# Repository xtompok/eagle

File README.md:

eagle
=====

Eagle files for various projects

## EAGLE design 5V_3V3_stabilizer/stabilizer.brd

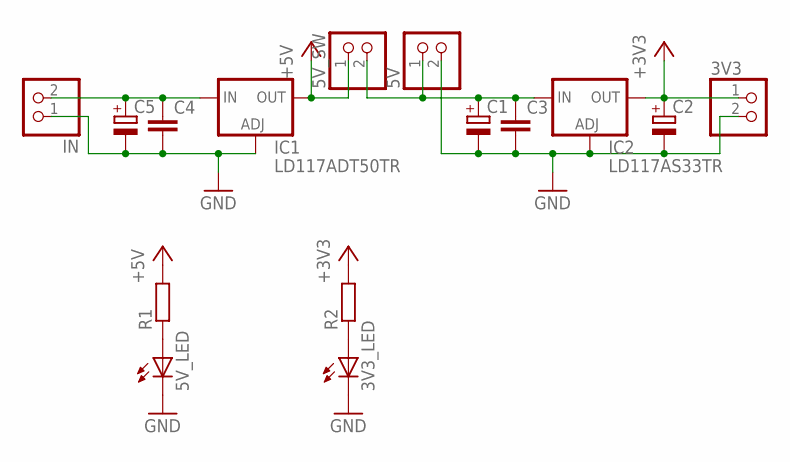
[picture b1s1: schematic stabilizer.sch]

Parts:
3V3, 5V, 5V_SW: PINHD-1X2; 1X02
3V3_LED, 5V_LED: LEDSML0805; SML0805
C1, C2, C5: CPOL-EUD; PANASONIC_D
C3, C4: C-EUC0805; C0805
IC1: LD117ADT50TR; DPACK
IC2: LD117AS33TR; SOT223
IN: PINHD-1X2; 1X02
R1, R2: R-EU_R0805; R0805

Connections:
+3V3: 3V3.1, C2.+, IC2.4 (OUT), R2.2
+5V: 5V_SW.1, IC1.4 (OUT), R1.2
GND: 3V3.2, 3V3_LED.C, 5V.2, 5V_LED.C, C1.-, C2.-, C3.2, C4.2, C5.-, IC1.1 (ADJ), IC2.1 (ADJ), IN.1
unnamed: 5V_LED.A, R1.1
unnamed: 3V3_LED.A, R2.1
unnamed: C4.1, C5.+, IC1.3 (IN), IN.2
unnamed: 5V.1, 5V_SW.2, C1.+, C3.1, IC2.3 (IN)

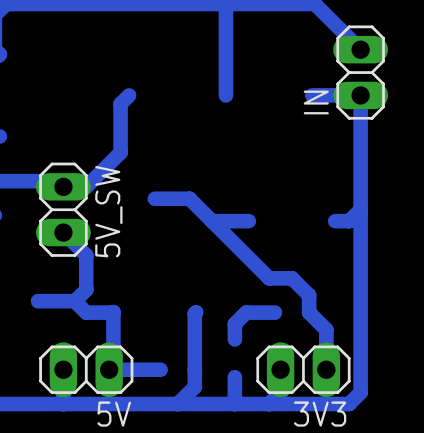
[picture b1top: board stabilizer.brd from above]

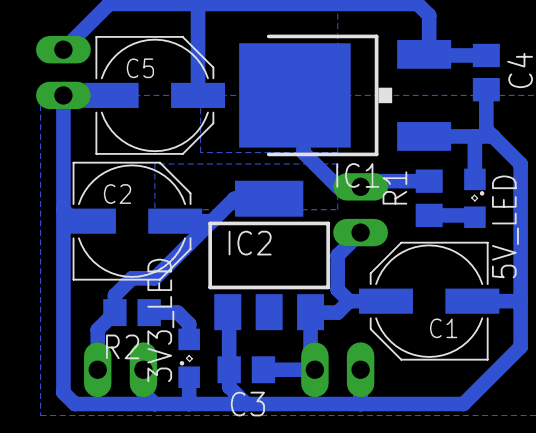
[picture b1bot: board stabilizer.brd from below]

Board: 2 copper layers, 15 parts (11 on the bottom side), 7 nets.

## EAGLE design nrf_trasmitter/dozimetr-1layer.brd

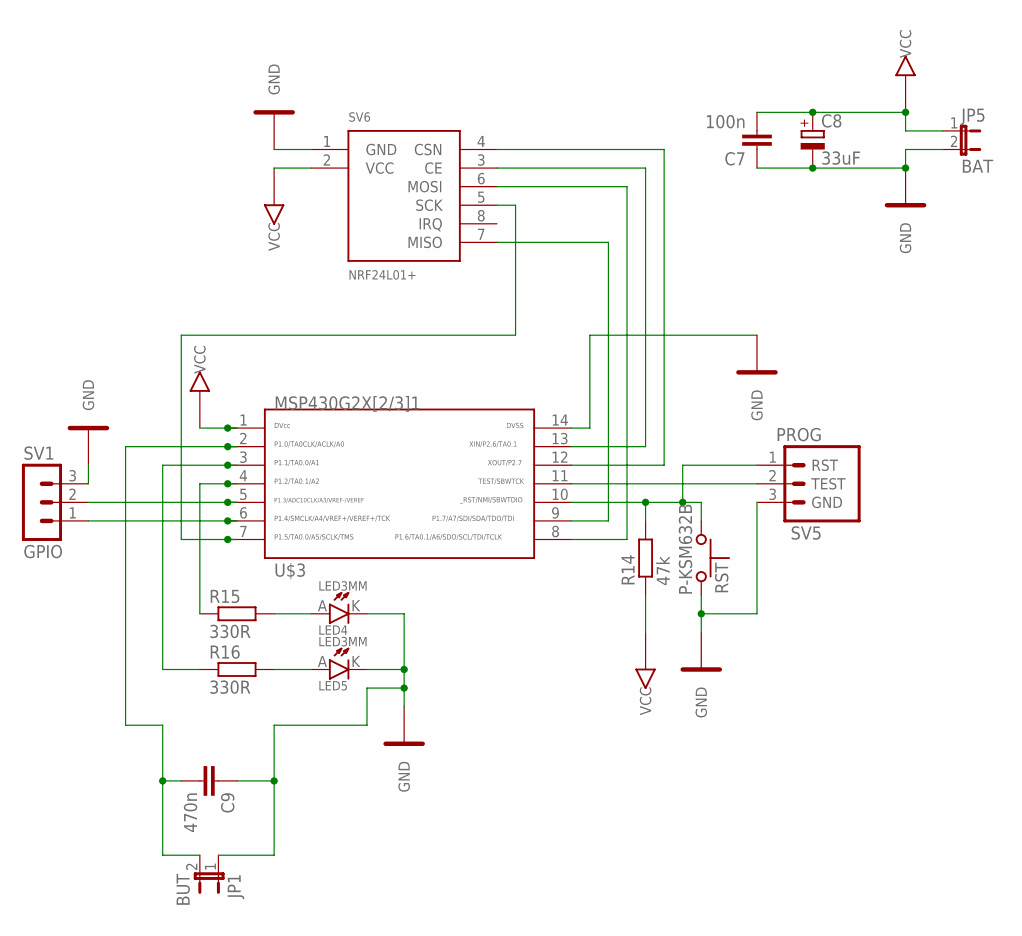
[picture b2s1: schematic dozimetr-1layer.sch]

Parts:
C7: 100n; C0805
C8: 33uF; E2,5-6E
C9: 470n; C0805K
JP1: BUT; JP1
JP5: BAT; JP1
LED4, LED5: LED3MM
R14: 47k; R0805
R15, R16: 330R; R0805
RST: P-KSM632B
SV1: GPIO; MA03-1
SV5: PROG; MA03-1
SV6: NRF24L01+; NRF24L01_MOD
U$3: G2X[2/3]1---PW14; PW14

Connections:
GND: C7.1, C8.-, C9.1, JP1.1, JP5.2, LED4.K (C), LED5.K (C), RST.2, SV1.3, SV5.3 (GND), SV6.1 (GND), U$3.14
unnamed: C9.2, JP1.2, U$3.2
unnamed: SV1.2, U$3.5
unnamed: SV1.1, U$3.6
unnamed: SV5.2 (TEST), U$3.11
unnamed: R14.2, RST.1, SV5.1 (RST), U$3.10
unnamed: SV6.7 (MISO), U$3.9
unnamed: SV6.6 (MOSI), U$3.8
unnamed: SV6.5 (SCK), U$3.7
unnamed: R15.1, U$3.4
unnamed: LED4.A, R15.2
unnamed: SV6.3 (CE), U$3.13
unnamed: SV6.4 (CSN), U$3.12
unnamed: R16.1, U$3.3
unnamed: LED5.A, R16.2
VCC: C7.2, C8.+, JP5.1, R14.1, SV6.2 (VCC), U$3.1

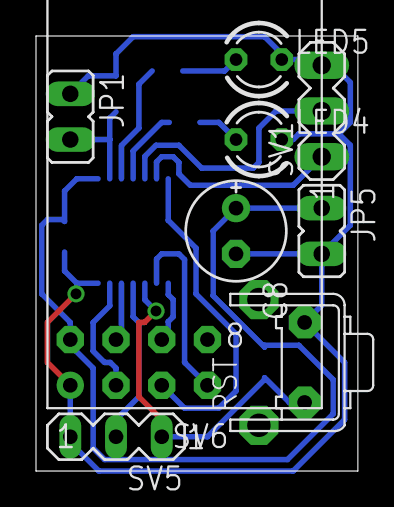
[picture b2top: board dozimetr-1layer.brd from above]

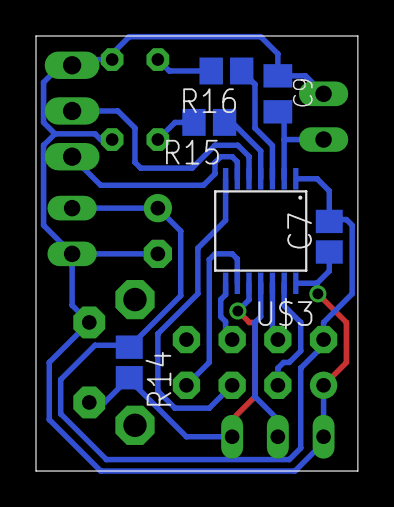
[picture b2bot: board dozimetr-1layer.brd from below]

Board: 2 copper layers, 17.9 x 24.2 mm, 15 parts (6 on the bottom side), 16 nets.

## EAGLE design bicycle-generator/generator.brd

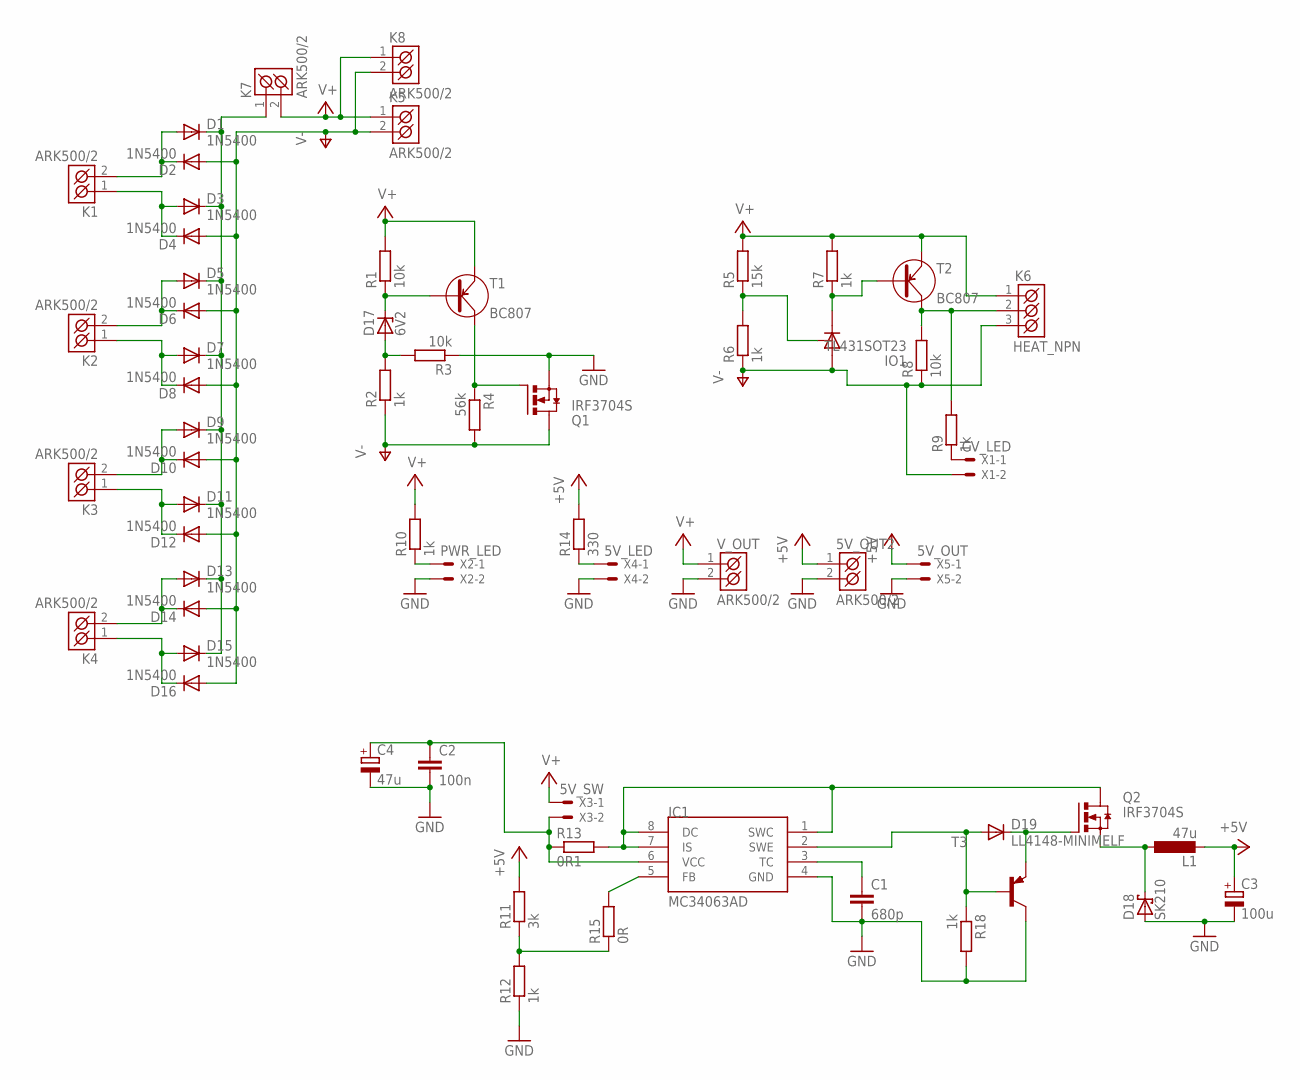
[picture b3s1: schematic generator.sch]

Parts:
5V_OUT2: ARK500/2
C1: 680p; C0805
C2: 100n; C0805
C3: 100u; PANASONIC_D
C4: 47u; PANASONIC_D
D1, D2, D3, D4, D5, D6, D7, D8, D9, D10, D11, D12, D13, D14, D15, D16: 1N5400; DO201-15
D17: 6V2; SOD80C
D18: SK210; SMB
D19: LL4148-MINIMELF; SOD80C
IC1: MC34063AD; SOIC8
IO1: TL431SOT23; SOT23
K1, K2, K3, K4, K5, K7, K8: ARK500/2
K6: HEAT_NPN; ARK500/3
L1: 47u; TJ3-U1
Q1, Q2: IRF3704S; D2PACK
R1, R3, R8: 10k; R0805
R2, R6, R7, R9, R10, R12, R18: 1k; R0805
R4: 56k; R0805
R5: 15k; R0805
R11: 3k; R0805
R13: 0R1; R0805
R14: 330; R0805
R15: 0R; R1206
T1, T2: BC807; SOT-23
T3: BC807-16-PNP-SOT23-BEC; SOT23-BEC
V_OUT: ARK500/2
X1: CV_LED; 22-23-2021
X2: PWR_LED; 22-23-2021
X3: 5V_SW; 22-23-2021
X4: 5V_LED; 22-23-2021
X5: 5V_OUT; 22-23-2021

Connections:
+5V: 5V_OUT2.1 (K1), C3.+, L1.2, R11.2, R14.2, X5.1
GND: 5V_OUT2.2 (K2), C1.2, C2.2, C3.-, C4.-, D18.A, IC1.4 (GND), Q1.3 (S), R3.1, R12.1, R18.2, T3.C, V_OUT.2 (K2), X2.2, X4.2, X5.2
unnamed: D1.A, D2.C, K1.2 (K2)
unnamed: D3.A, D4.C, K1.1 (K1)
unnamed: IO1.1 (C), R7.1, T2.1 (B)
unnamed: Q1.1 (G), R4.1, T1.3 (C)
unnamed: D5.A, D6.C, K2.2 (K2)
unnamed: D7.A, D8.C, K2.1 (K1)
unnamed: K6.2 (K2), R8.2, R9.2, T2.3 (C)
unnamed: R9.1, X1.1
unnamed: D9.A, D10.C, K3.2 (K2)
unnamed: D11.A, D12.C, K3.1 (K1)
unnamed: R11.1, R12.2, R15.1
unnamed: IO1.2 (R), R5.1, R6.2
unnamed: D13.A, D14.C, K4.2 (K2)
unnamed: D15.A, D16.C, K4.1 (K1)
unnamed: D19.C, Q2.1 (G), T3.E
unnamed: C1.1, IC1.3 (TC)
unnamed: D17.C, R1.1, T1.1 (B)
unnamed: D17.A, R2.2, R3.2
unnamed: D18.C, L1.1, Q2.3 (S)
unnamed: D1.C, D3.C, D5.C, D7.C, D9.C, D11.C, D13.C, D15.C, K7.1 (K1)
unnamed: IC1.5 (FB), R15.2
unnamed: R14.1, X4.1
unnamed: R10.1, X2.1
unnamed: C2.1, C4.+, IC1.6 (VCC), R13.1, X3.2
unnamed: IC1.1 (SWC), IC1.7 (IS), IC1.8 (DC), Q2.2 (D), R13.2
unnamed: D19.A, IC1.2 (SWE), R18.1, T3.B
V+: K5.1 (K1), K6.1 (K1), K7.2 (K2), K8.1 (K1), R1.2, R5.2, R7.2, R10.2, T1.2 (E), T2.2 (E), V_OUT.1 (K1), X3.1
V-: D2.A, D4.A, D6.A, D8.A, D10.A, D12.A, D14.A, D16.A, IO1.3 (A), K5.2 (K2), K6.3 (K3), K8.2 (K2), Q1.2 (D), R2.1, R4.2, R6.1, R8.1, X1.2

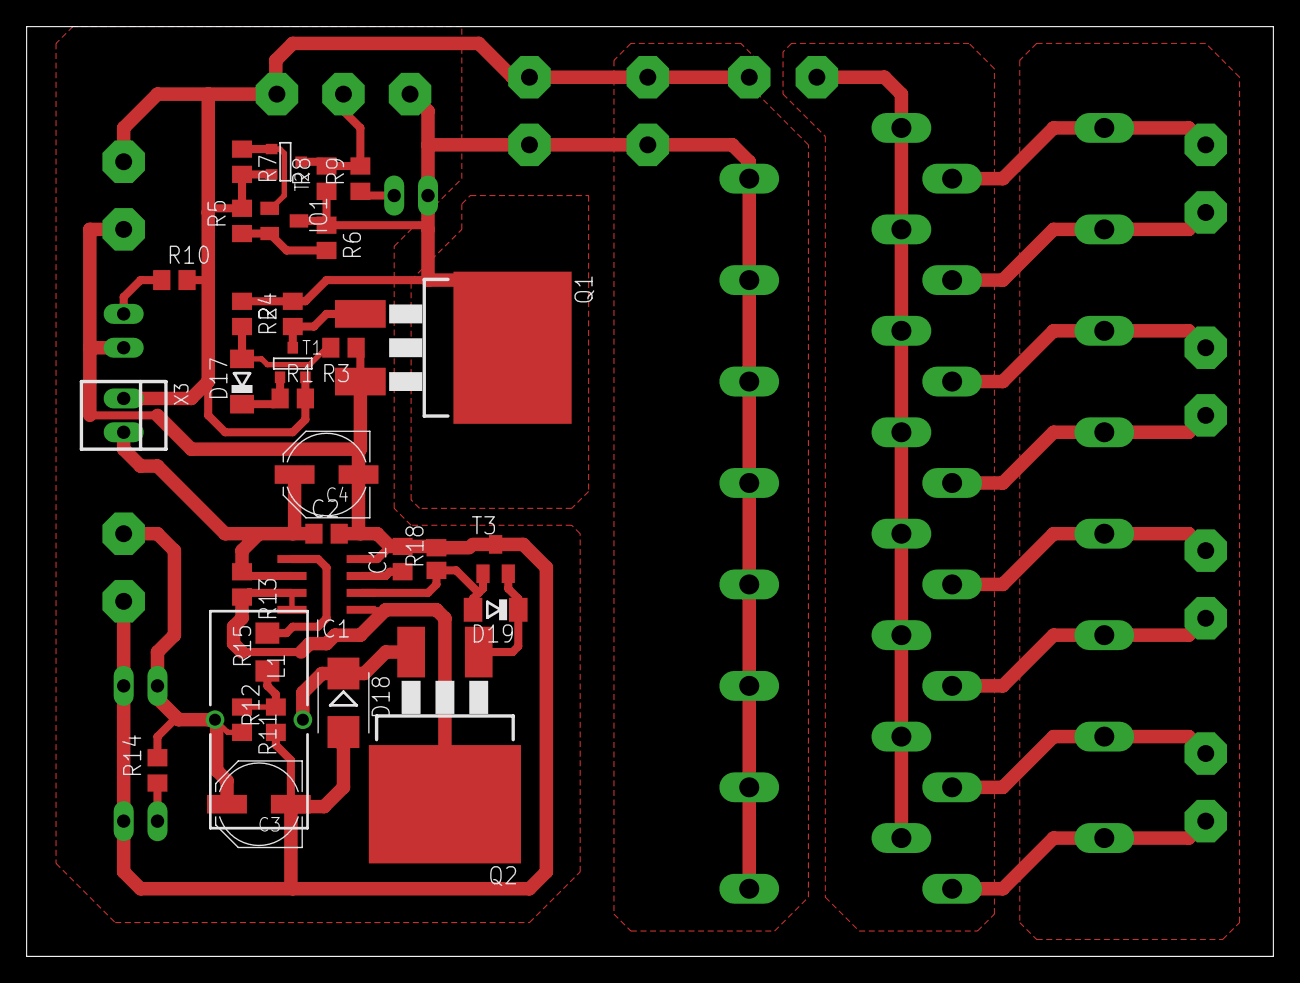
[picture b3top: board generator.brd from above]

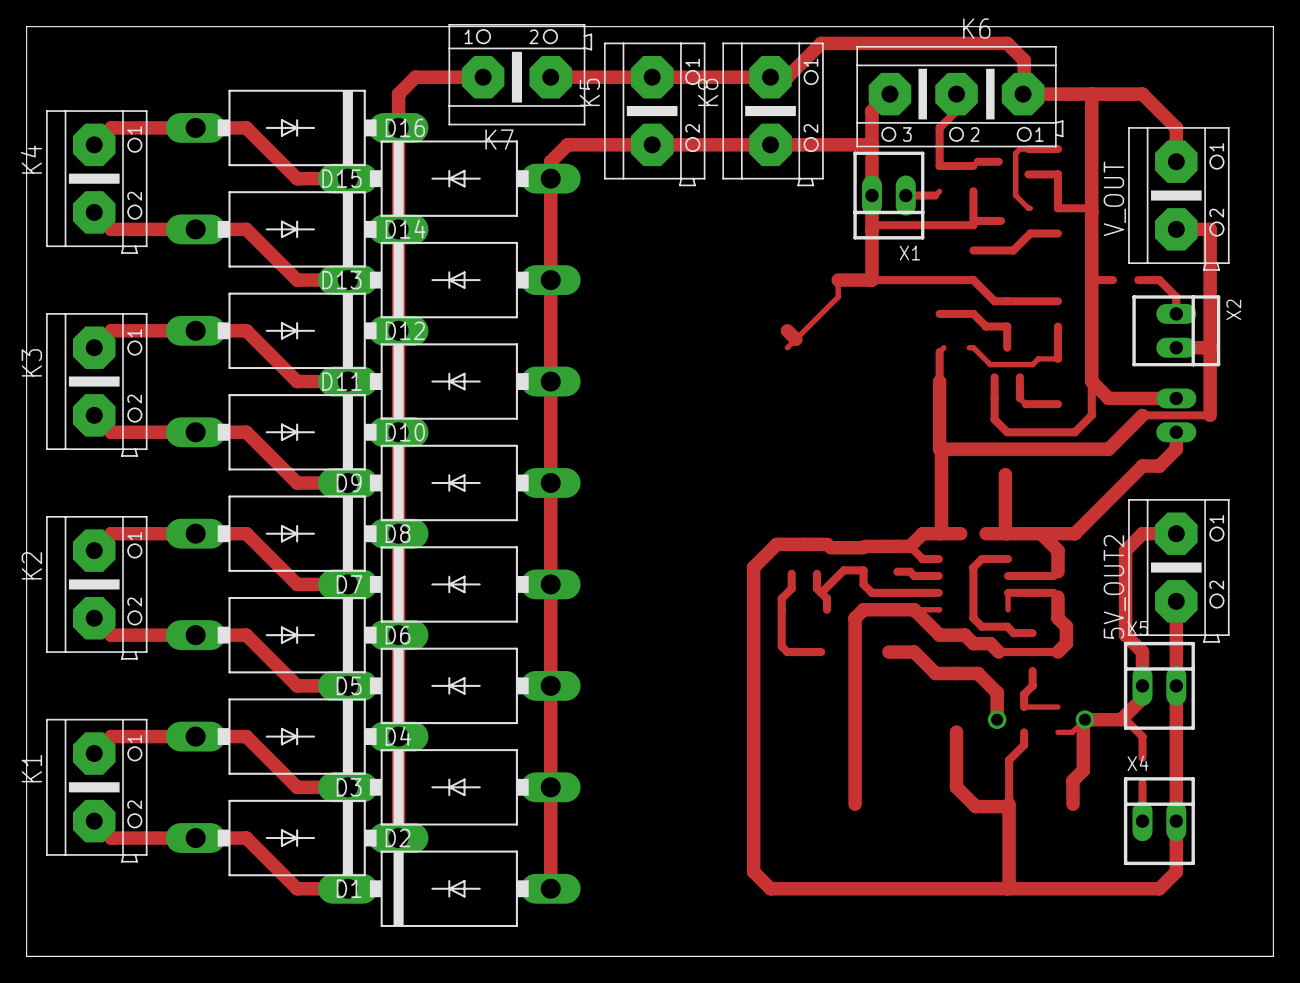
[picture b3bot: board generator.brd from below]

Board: 2 copper layers, 93.7 x 69.8 mm, 62 parts (30 on the bottom side), 30 nets.

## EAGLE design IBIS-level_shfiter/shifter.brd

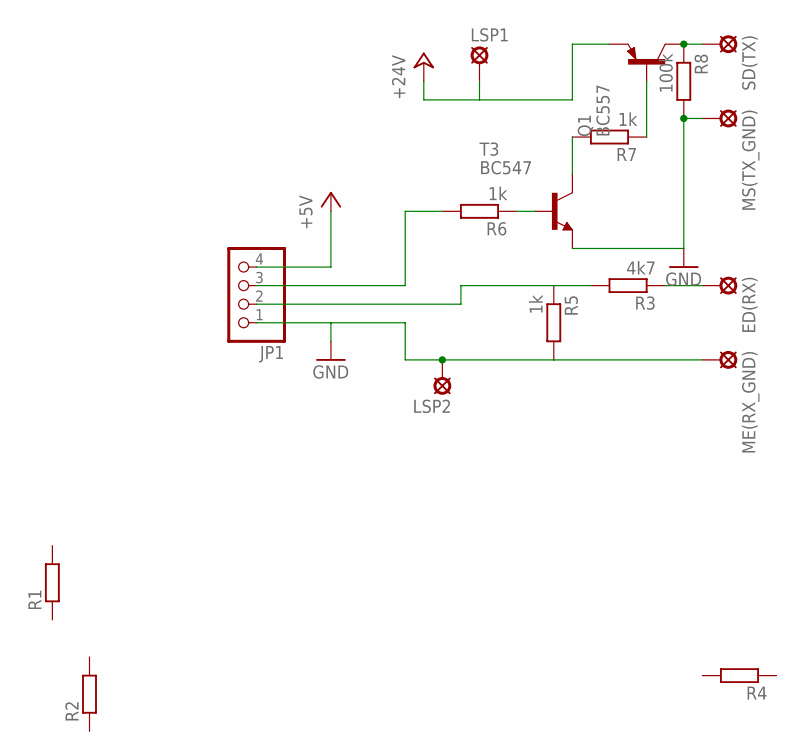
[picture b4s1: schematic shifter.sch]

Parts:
ED(RX): LSP10
JP1: PINHD-1X4; 1X04
LSP1, LSP2: LSP10
ME(RX_GND): LSP10
MS(TX_GND): LSP10
Q1: BC557; TO92
R1, R2, R4: R-EU_M0805; M0805
R3: 4k7; M0805
R5, R6, R7: 1k; M0805
R8: 100k; M0805
SD(TX): LSP10
T3: BC547; TO92

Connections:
+5V: JP1.4
+24V: LSP1.MP, Q1.1 (E)
GND: JP1.1, LSP2.MP, ME(RX_GND).MP, MS(TX_GND).MP, R5.2, R8.2, T3.1 (E)
unnamed: ED(RX).MP, R3.1
unnamed: JP1.2, R3.2, R5.1
unnamed: JP1.3, R6.2
unnamed: R6.1, T3.2 (B)
unnamed: R7.2, T3.3 (C)
unnamed: Q1.2 (B), R7.1
unnamed: Q1.3 (C), R8.1, SD(TX).MP

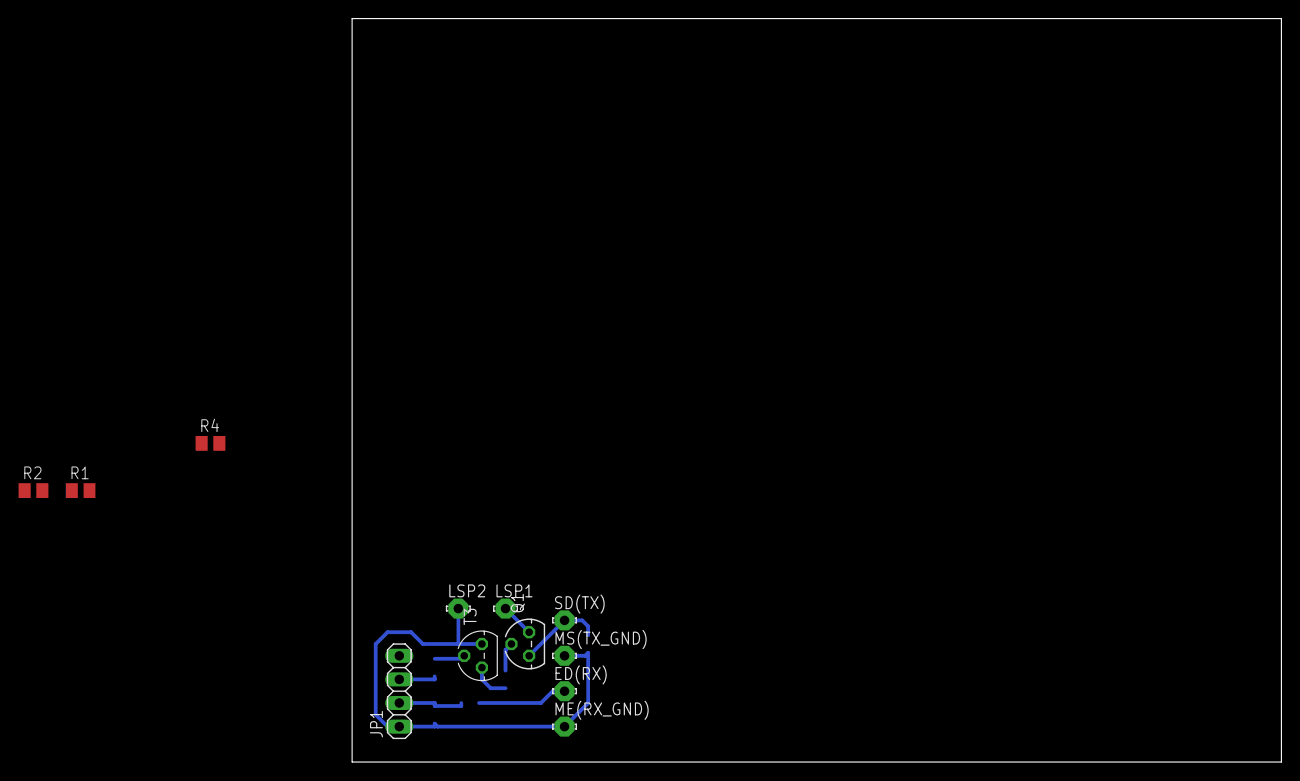
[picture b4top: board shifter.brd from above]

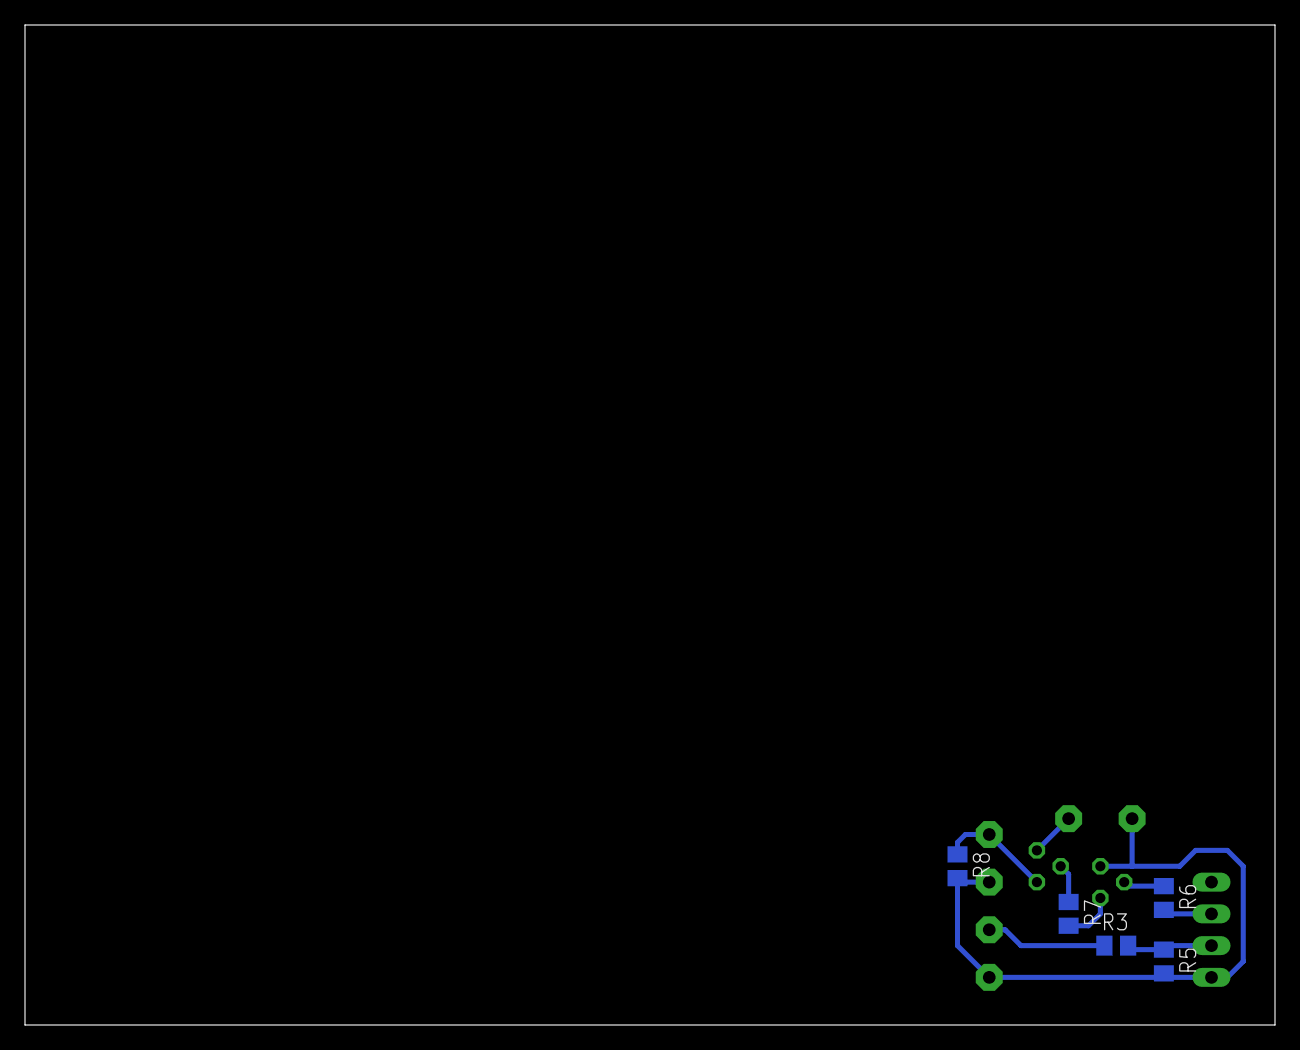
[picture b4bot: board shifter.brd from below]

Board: 2 copper layers, 100.0 x 80.0 mm, 17 parts (5 on the bottom side), 9 nets.

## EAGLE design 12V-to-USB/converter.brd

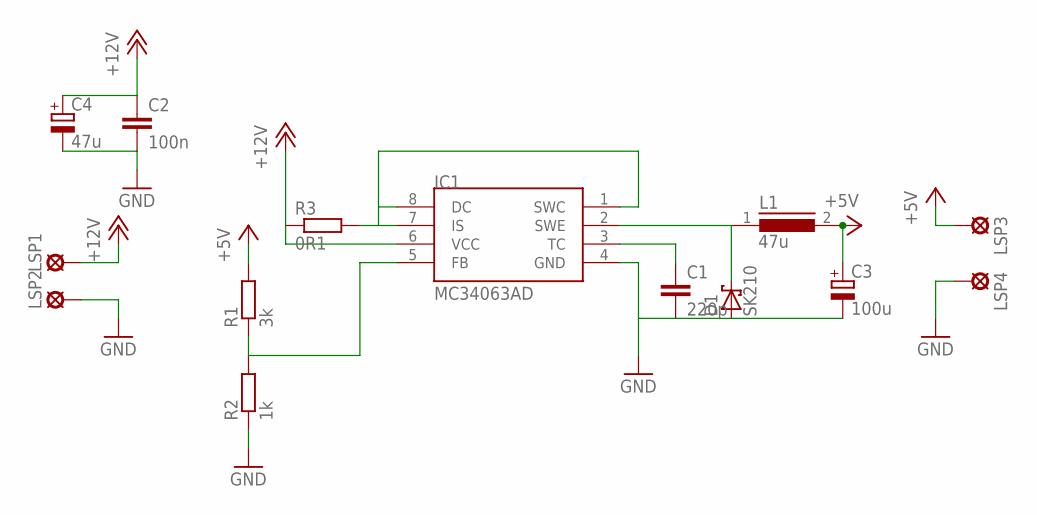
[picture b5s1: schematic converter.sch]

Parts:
C1: 220p; C0805
C2: 100n; C0805
C3: 100u; PANASONIC_D
C4: 47u; PANASONIC_D
D1: SK210; SMB
IC1: MC34063AD; SOIC8
L1: 47u; DR127
LSP1: +12V; LSP11
LSP2: GND; LSP11
LSP3, LSP4: LSP11
R1: 3k; R0805
R2: 1k; R0805
R3: 0R1; R0805

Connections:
+5V: C3.+, L1.2, LSP3.MP, R1.2
+12V: C2.1, C4.+, IC1.6 (VCC), LSP1.MP, R3.1
GND: C1.2, C2.2, C3.-, C4.-, D1.A, IC1.4 (GND), LSP2.MP, LSP4.MP, R2.1
unnamed: IC1.5 (FB), R1.1, R2.2
unnamed: IC1.1 (SWC), IC1.7 (IS), IC1.8 (DC), R3.2
unnamed: C1.1, IC1.3 (TC)
unnamed: D1.C, IC1.2 (SWE), L1.1

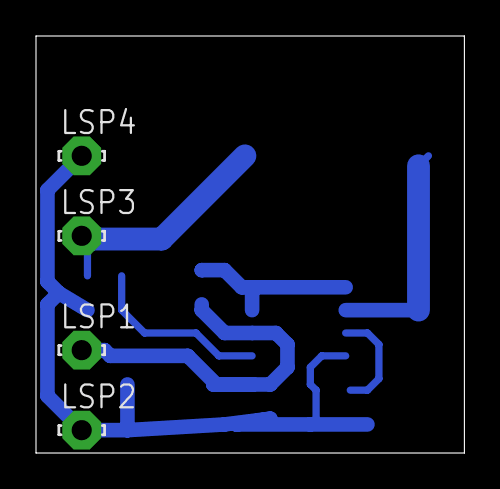
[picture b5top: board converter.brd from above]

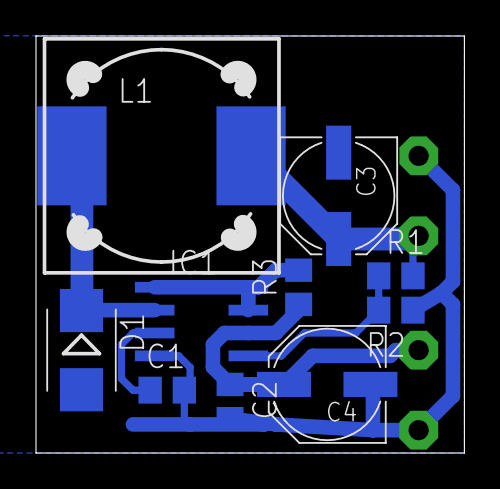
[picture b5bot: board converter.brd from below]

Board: 2 copper layers, 23.8 x 23.2 mm, 14 parts (10 on the bottom side), 7 nets.

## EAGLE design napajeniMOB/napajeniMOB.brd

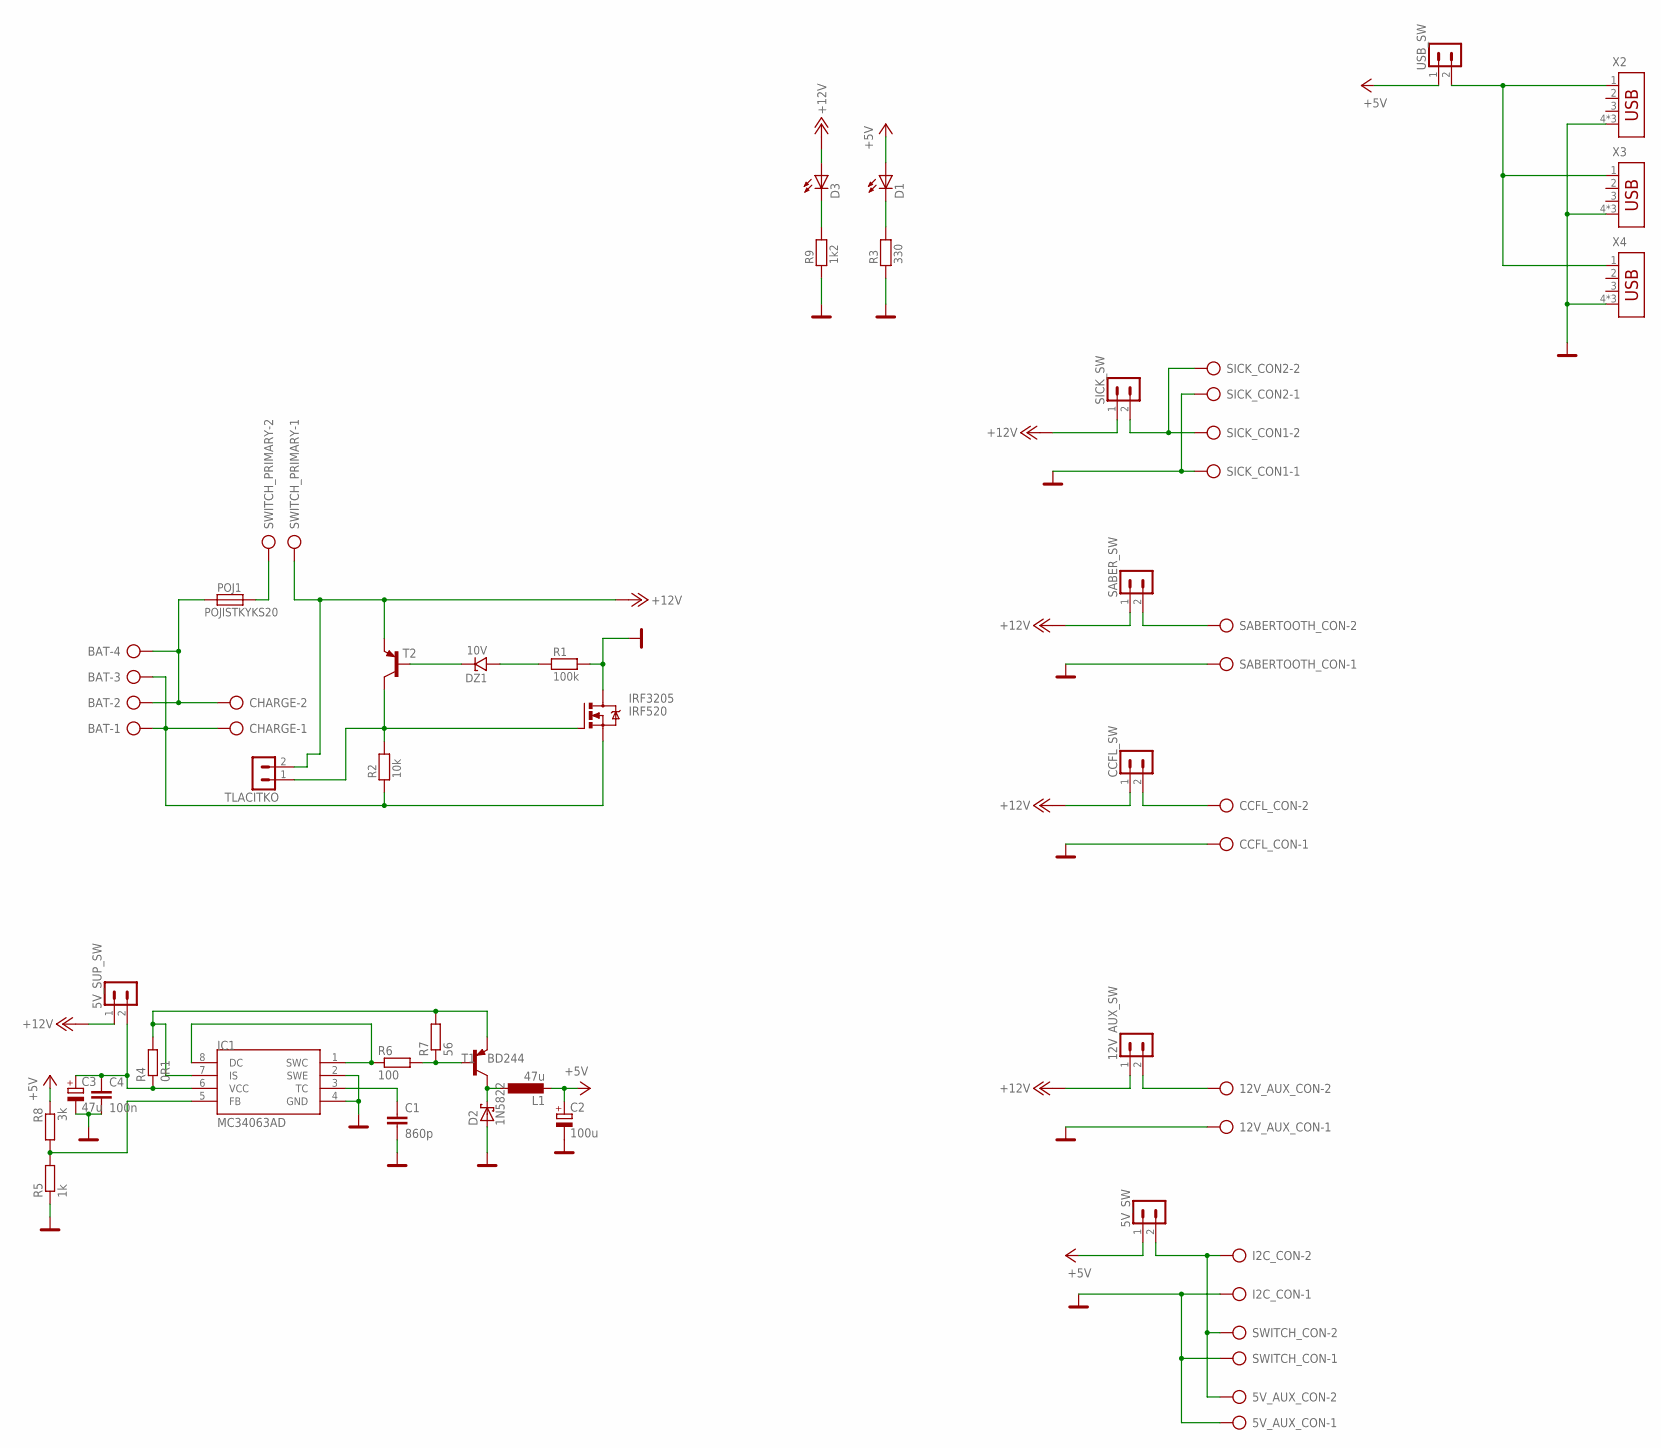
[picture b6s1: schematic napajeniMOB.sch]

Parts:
5V_AUX_CON, 12V_AUX_CON: AK500/2
5V_SUP_SW, 5V_SW, 12V_AUX_SW: PSH02-02P
BAT: AK500/4
C1: 860p; C0805
C2: 100u; E5-8,5
C3: 47u; E5-8,5
C4: 100n; C0805
CCFL_CON: AK500/2
CCFL_SW: PSH02-02P
CHARGE: AK500/2
D1, D3: LED3MM
D2: 1N5822; DO41-7.6
DZ1: 10V; SOD-80
I2C_CON: AK500/2
IC1: MC34063AD; SOIC8
IRF3205: IRF520; TO220BV
L1: 47u; TJ3-U1
POJ1: POJISTKYKS20; POJ_KS20
R1: 100k; 0805
R2: 10k; 0805
R3: 330; 0805
R4: 0R1; M0805
R5: 1k; M0805
R6: 100; M0805
R7: 56; M0805
R8: 3k; M0805
R9: 1k2; 0805
SABERTOOTH_CON: AK500/2
SABER_SW: PSH02-02P
SICK_CON1, SICK_CON2: AK500/2
SICK_SW: PSH02-02P
SWITCH_CON: AK500/2
SWITCH_PRIMARY: AK500/2
T1: BD244; TO220
T2: BC807-16-PNP-SOT23-BEC; SOT23-BEC
TLACITKO: PSH02-02P
USB_SW: PSH02-02P
X2, X3, X4: USB-787616GROUNDED; USBGROUNDED

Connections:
+5V: 5V_SW.1, C2.+, D1.A, L1.2, R8.1, USB_SW.1
+12V: 5V_SUP_SW.1, 12V_AUX_SW.1, CCFL_SW.1, D3.A, SABER_SW.1, SICK_SW.1, SWITCH_PRIMARY.1, T2.E, TLACITKO.2
GND: 5V_AUX_CON.1, 12V_AUX_CON.1, C1.2, C2.-, C3.-, C4.2, CCFL_CON.1, D2.A, I2C_CON.1, IC1.2 (SWE), IC1.4 (GND), IRF3205.D, R1.2, R3.1, R5.1, R9.1, SABERTOOTH_CON.1, SICK_CON1.1, SICK_CON2.1, SWITCH_CON.1, X2.4, X2.S1 (4), X2.S2 (4), X3.4, X3.S1 (4), X3.S2 (4), X4.4, X4.S1 (4), X4.S2 (4)
GND_BATERIE: BAT.1, BAT.3, CHARGE.1, IRF3205.S, R2.1
unnamed: DZ1.A, R1.1
unnamed: BAT.2, BAT.4, CHARGE.2, POJ1.1
unnamed: DZ1.K, T2.B
unnamed: POJ1.2, SWITCH_PRIMARY.2
unnamed: IRF3205.G, R2.2, T2.C, TLACITKO.1
unnamed: 5V_SUP_SW.2, C3.+, C4.1, IC1.6 (VCC), R4.1
unnamed: D3.K (C), R9.2
unnamed: D1.K (C), R3.2
unnamed: SICK_CON1.2, SICK_CON2.2, SICK_SW.2
unnamed: USB_SW.2, X2.1, X3.1, X4.1
unnamed: SABERTOOTH_CON.2, SABER_SW.2
unnamed: CCFL_CON.2, CCFL_SW.2
unnamed: D2.C, L1.1, T1.2 (C)
unnamed: 12V_AUX_CON.2, 12V_AUX_SW.2
unnamed: 5V_AUX_CON.2, 5V_SW.2, I2C_CON.2, SWITCH_CON.2
unnamed: IC1.5 (FB), R5.2, R8.2
unnamed: IC1.7 (IS), R4.2, R7.2, T1.3 (E)
unnamed: IC1.1 (SWC), IC1.8 (DC), R6.1
unnamed: R6.2, R7.1, T1.1 (B)
unnamed: C1.1, IC1.3 (TC)

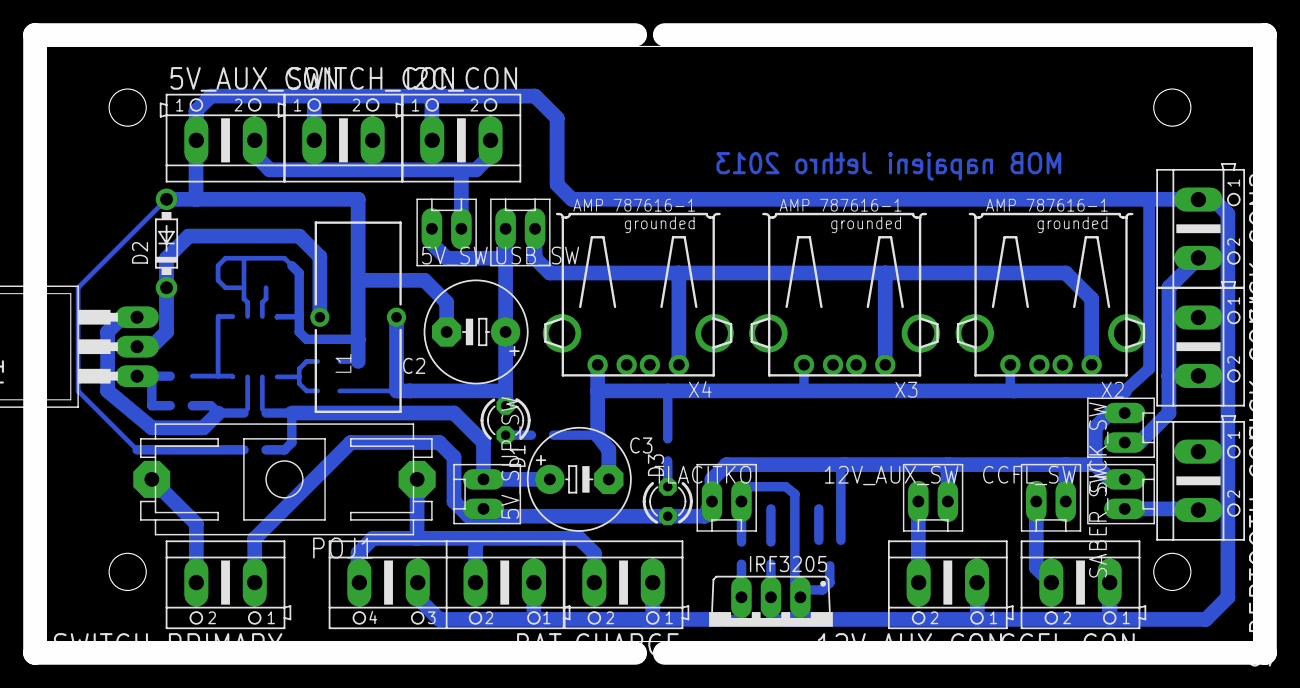
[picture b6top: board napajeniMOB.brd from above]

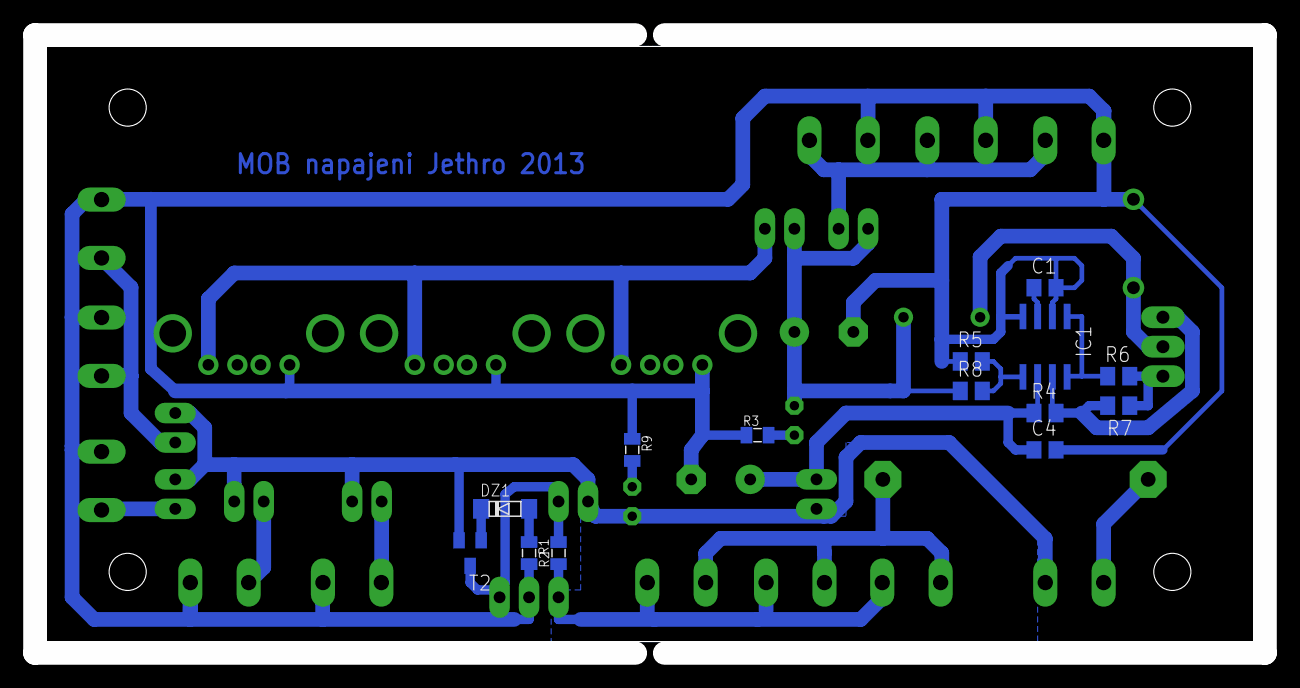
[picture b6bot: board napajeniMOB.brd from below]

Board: 2 copper layers, 106.0 x 53.3 mm, 45 parts (14 on the bottom side), 24 nets.

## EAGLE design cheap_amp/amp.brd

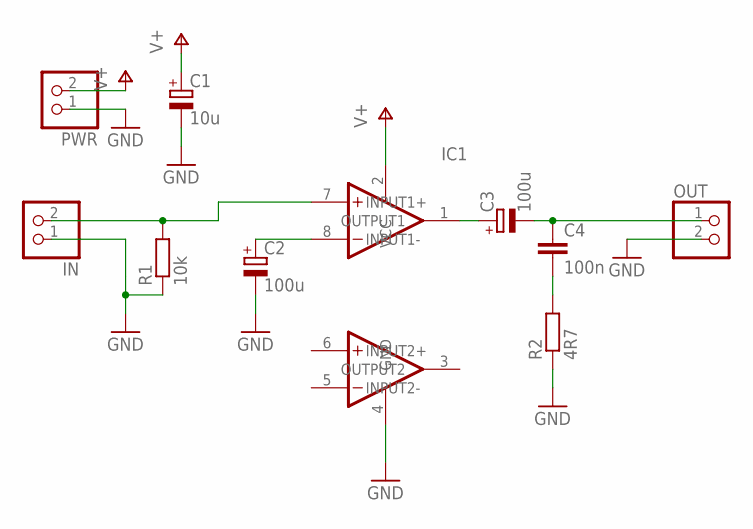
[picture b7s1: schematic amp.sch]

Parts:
C1: 10u; E2,5-5
C2, C3: 100u; E2,5-5
C4: 100n; C0805
IC1: TDA2822M; DIL8
IN: PINHD-1X2; 1X02
OUT: PINHD-1X2; 1X02
PWR: PINHD-1X2; 1X02
R1: 10k; R0805
R2: 4R7; R0805

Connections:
GND: C1.-, C2.-, IC1.4 (GND), IN.1, OUT.2, PWR.1, R1.1, R2.1
unnamed: IC1.7 (INPUT1+), IN.2, R1.2
unnamed: C2.+, IC1.8 (INPUT1-)
unnamed: C3.+, IC1.1 (OUTPUT1)
unnamed: C3.-, C4.1, OUT.1
unnamed: C4.2, R2.2
V+: C1.+, IC1.2 (VCC), PWR.2

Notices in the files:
parts and their libraries:
Copyright (C) PaJa 2011
Copyright (C) PaJa 2001-2011
Copyright (C) Vlada 2004-2005
